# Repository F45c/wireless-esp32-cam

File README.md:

# Wireless Esp32-Camera using nRF24l01+

### What is it?

I'm building a wireless esp32 camera that uses the 2.4 GHZ RF chip nRF24l01+ to transmit the images over a greater distance than just WIFI. Using the Ebyte E01 2G4M27D Module achieving distances up to 3000 meters, I can receive images and change the resolution and quality of the captures from the receiver side.

### But Why?

My Wifi signal doesn't cover my entire property so I figured I will build a security camera that has a higher distance and can be placed on the edge where no normal camera would get a connection.
Also, out on my field, I can monitor all my stuff that's stored there from home and watch the animals walk around at night from a few hundred meters away.

### Build

These are the PCBs with the modules plugged into the PinSockets

This is the finished build with the camera and antennas and its working great!

The final build is way faster than the prototype and reaches a lot further even through walls.

### How it works

#### The Transmitter
The image is captured and divided into chunks of 32 bytes.

Then those chunks are split into 16 byte chunks for separately encrypting them using AES-128 (symmetric encryption).

Those chunks are transmitted on 2.4 ghz on a high channel like 74 preventing conflicts with wifi.

The nRF24 uses a proprietary protocol with GFSK (Gaussian Frequency Shift Keying).

#### The Receiver
The receiver separates the 32 byte chunks into 16 byte chunks for decryption following the transmission over Serial to the Computer.

The Computer runs a python script saving the data to an image file.

### 3D Model

### Prototyping

Using some cheaper modules and some perfboards, I made a prototype which I used to transmit and receive this image.

It's still low quality because of the bad prototype hardware. The highest distance I achieved with the prototype was ~100m line-of-sight and in another test, the signal was able to pass through two walls (steel-concrete 30cm) without much data loss.

These are the speeds the prototype achieved.

|Resolution & Quality|	Time|	FPS|
|--------------|----|----|
|160x120 + low jpeg quality| <1s|	~2.5|
320x240 + low jpeg quality|	~1.5s	| ~0.6|
480x320 + low jpeg quality|	~3s|	~0.3|
800x600 + little higher quality| ~15s| ~0.07|
1600x1200 + low jpeg quality|	~50s|	~0.02|

The final build with the PCB should be able to send higher quality and resolution images with less error rate and faster speeds. How fast the 2G4M27D is impossible to know but I'm assuming an increase of at least 30% in transmission speed. 

Since the datasheet claims a range of 5000m LOS, I'm assuming that the final build will achieve a functioning range of about 2500m LOS when placing the antennas correctly at a high place. This would be definitely enough for my use case.

### Schematic

I use PinSockets for both the Esp32 and the 2G4M27D and PinHeaders for the Esp32 UART interface. I added two pads for the 3.7v lithium ion battery and it's connected to the VCC pin of the Esp32 which is internally converted into 3.3v for the output pin.

This is the Pinout:
|Esp32|2G4M27D|
|-----|------|
|3V3|3V3|
|GND|GND|
|GPIO12|CE|
|GPIO33|CNS|
|GPIO14|SCK|
|GPIO25|MOSI|
|GPIO27|MISO|
|GPIO26|IRQ|

### PCB Design

### BOM

|Name|Purpose|Quantity|Total Cost (USD)|Link|Distributor|
|----|------|---|------|------------|-----------|
|3.7v LiPo battery|Battery for transmitter|1|21.18|https://www.conrad.de/de/p/akyga-lp675568-akkupack-x-spezial-akku-lipo-3-7-v-3500-mah-3385862.html|Conrad|
|PCB|PCB for both receiver and transmitter|1|5.5||JLCPCB|
|Esp32 38 pin|Receiver Esp32|1|5.73|https://de.aliexpress.com/item/1005006613312645.html|Aliexpress|
|Esp32 Wrover Cam OV5640|Capturing images and computing transmission|1|9|https://de.aliexpress.com/item/1005006705436186.html|Aliexpress|
|2 pieces Ebyte E01-2G4M27D|One for transmitter, one for receiver|1|11.9|https://de.aliexpress.com/item/1005003212341678.html|Aliexpress|

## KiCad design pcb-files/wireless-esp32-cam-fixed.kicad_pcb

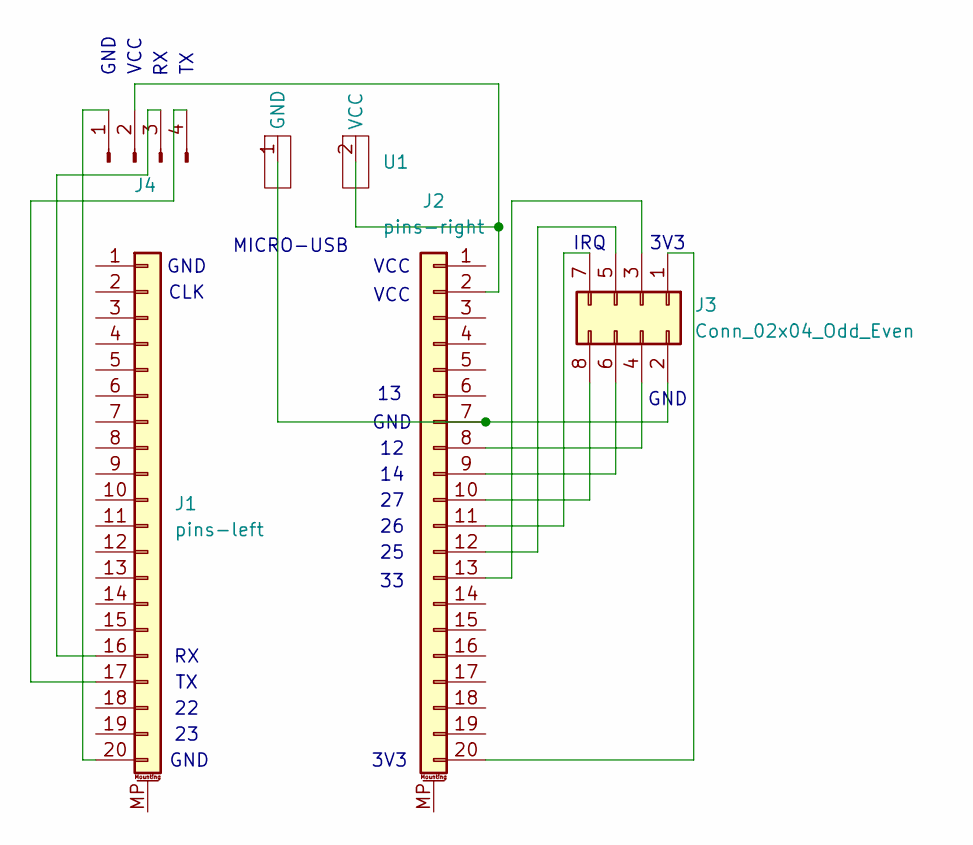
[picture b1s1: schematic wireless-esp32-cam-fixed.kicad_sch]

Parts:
J1: pins-left; PinSocket_1x20_P2.54mm_Vertical
J2: pins-right; PinSocket_1x20_P2.54mm_Vertical
J3: Conn_02x04_Odd_Even; PinSocket_2x04_P2.54mm_Vertical
J4: Conn_01x04_Pin; PinHeader_1x04_P2.54mm_Vertical
U1: solder-pad

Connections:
unnamed: J1.16, J4.3
unnamed: J1.17, J4.4
unnamed: J1.20, J4.1
unnamed: J2.2, J4.2, U1.2 (VCC)
unnamed: J2.7, J3.2, U1.1 (GND)
unnamed: J2.8, J3.4
unnamed: J2.9, J3.6
unnamed: J2.10, J3.8
unnamed: J2.11, J3.7
unnamed: J2.12, J3.5
unnamed: J2.13, J3.3
unnamed: J2.20, J3.1

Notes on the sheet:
GND
VCC
CLK
3V3
MICRO-USB
IRQ

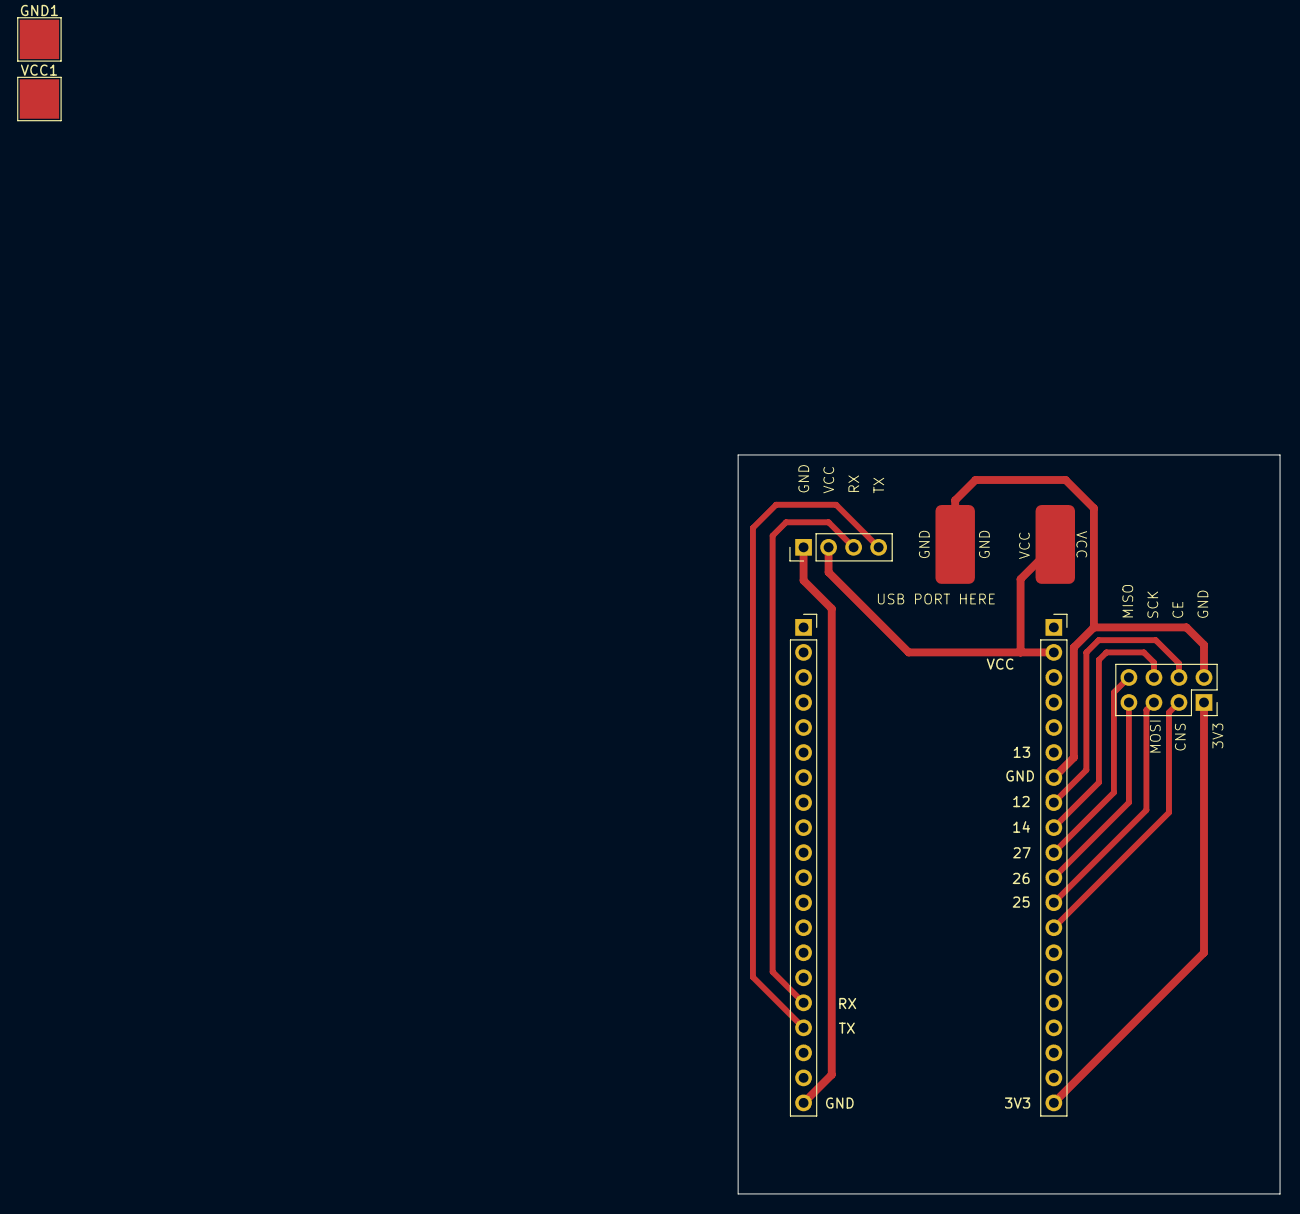
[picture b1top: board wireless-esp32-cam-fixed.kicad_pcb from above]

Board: 2 copper layers, 55.0 x 75.0 mm, 7 parts (0 on the bottom side), 12 nets.

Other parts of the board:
GND1: MountingHole; TestPoint_Pad_4.0x4.0mm
VCC1: MountingHole; TestPoint_Pad_4.0x4.0mm

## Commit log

2026-04-06 minimal transmitter code for sending the images
2026-04-06 added a simple receiver code
2026-04-06 added the python script that reads serial and saves the image
2026-04-07 added photo of transmitter perfboard 3d model
2026-04-12 added schematic, pcb and 3d model images
2026-04-17 added new firmware code
2026-04-19 added step file and 3d model
2026-04-19 added pcb files
2026-04-19 added final pcb design images
2026-04-19 added 3d model images
2026-04-19 added bom
2026-04-19 added battery to bom
2026-05-06 Adding Functionality Explanation to Readme
    I added a more in depth explanation on how exactly the transmission process works
2026-05-06 added transmission diagram
2026-05-06 added pcb model with esp32 wrover
2026-05-06 added an image
2026-05-14 added schematic image
2026-05-14 Added Prototype Testing Data and Schematic explanation
2026-06-30 added build images
2026-06-30 updated readme to include build details
